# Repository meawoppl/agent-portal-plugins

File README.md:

# Agent Portal Plugins

This repository is a collection of test and reference plugins for
[Agent Portal](https://github.com/meawoppl/agent-portal). Each plugin lives in a
subdirectory and contains its own `agent-portal-plugin.toml` manifest.

## Interface Design

Agent Portal owns the session lifecycle, agent launch, authentication, work
queues, docked surfaces, and plugin discovery UI. This repository owns
domain-specific plugin packages: manifests, skills, prompts, command shims,
managed toolchains, and optional HTTP workbench surfaces.

The interface is intentionally manifest-first:

- `[[detect]]` patterns let Portal suggest plugins for a working directory before
  an agent is launched.
- `[[skills]]` and `[[prompts]]` describe context Portal can inject into agent
  sessions, with visible context-cost accounting in the Portal UI.
- `[[commands]]` define safe, named command surfaces that Portal and agents can
  call without learning each plugin's private shell layout.
- `[surface]` describes an optional local HTTP app that Portal can start and dock
  beside the conversation.
- `[install]` and `[[toolchains]]` keep plugin setup and health checks inside
  the plugin package instead of hard-coding domain tooling into Portal.

This split keeps Agent Portal generic while still making plugin capability
discoverable in the launch menu, session header, plugin dock, and collapsed
plugin-context notice.

Install any plugin from its subdirectory:

```console
agent-portal plugin install github:meawoppl/agent-portal-plugins//kicadmium
agent-portal plugin install github:meawoppl/agent-portal-plugins//visilog
agent-portal plugin install github:meawoppl/agent-portal-plugins//unlinked
agent-portal plugin install github:meawoppl/agent-portal-plugins//yapcad
agent-portal plugin install github:meawoppl/agent-portal-plugins//slowbooks
```

## Plugins

- [`slowbooks`](slowbooks/) - project-local SlowBooks Pro bookkeeping with the
  native browser UI, persistent company files, scoped API commands, and managed
  startup/restarts.

- [`visilog`](visilog/) - interactive design exploration with the native
  Visilog viewer: module hierarchy diagrams, live values, source inspection,
  stepping, breakpoints and JSON design graphs.
- [`unlinked`](unlinked/) - Simulink model review without MATLAB via
  [Unlinked](https://github.com/CosmicFrontierLabs/unlinked): SVG diagrams
  and subsystems, block inventories, the supported simulation subset with
  plotted traces, and MATLAB-to-Rust transpilation.
- [`yapcad`](yapcad/) - parametric [yapCAD](https://github.com/rdevaul/yapCAD)
  DSL workbench: retained builds with stats and previews, a live 3D/2D pane
  with sections, measurement and pinned annotations, STL/STEP/DXF/SVG
  exports, `.ycpkg` packages and assemblies.
- [`kicadmium`](kicadmium/) - all-Rust KiCad PCB/electronics workbench: one
  binary with a browser workbench, `kct` (a native port of kicad-tools) and
  `kct lint`. It replaces the former `kicad-pcb` plugin and lived in
  `meawoppl/kicadmium` (now archived) before moving here with its full history.

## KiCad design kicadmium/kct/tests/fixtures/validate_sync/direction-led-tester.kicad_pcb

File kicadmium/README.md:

# kicadmium

> The heavy metal your PCBs were missing.

Cadmium is a heavy metal; kicadmium is the one your boards needed. It reads
your whole board, tells you your vias are ugly, and it's right. kicadmium is a
single Rust binary that wraps a real KiCad install with a browser workbench
(schematic, PCB, Gerbers, 3D, BOM, libraries, checks), fabrication export,
layout-quality audits, and a pile of agent skills. It does not ship KiCad.
Bring your own and turn it up.

## Quick start

As an Agent Portal plugin:

```sh
agent-portal plugin install github:meawoppl/agent-portal-plugins//kicadmium
```

Install builds the binary with `scripts/setup.sh`. Cargo writes to
`target/install-build`; only after a successful build does Rust atomically
activate the complete executable at `bin/kicadmium`. Every portal command uses
that stable path, so the previous executable remains callable throughout a
rebuild. `doctor --json` reports `runtime.installation.rebuild_in_progress`.
Concurrent installs are refused via `.install-lock/pid`; after an interrupted
install, check that PID is no longer running before removing the lock.

The portal gives plugin
commands a private `HOME`, so the script points rustup, cargo, trunk and
sccache at the account's existing caches (otherwise every install downloads a
toolchain and the crate index afresh) and uses `sccache` as the rustc wrapper
when it is installed. A reinstall then recompiles only what changed: about a
minute when nothing did, two with a `kct` change, versus twenty cold.
`KICADMIUM_SETUP_PLAIN=1` disables all of that.

From a checkout of this directory:

```sh
rustup target add wasm32-unknown-unknown
cargo install trunk --locked

cargo run -p backend -- serve --port 48888 --cwd /path/to/hardware/repo
# -> http://127.0.0.1:48888/
```

## CLI

```sh
kicadmium doctor --json --cwd .          # what tools/projects he found
kicadmium drc --json --cwd . --project board-a
kicadmium erc --json --cwd .
kicadmium quality --json --cwd .         # kct rules + in-house audits vs qualityProfile
kicadmium lint --json --cwd .            # = kct lint run on the project board
kicadmium export gerbers --cwd . --out build/gerbers
kicadmium export jlcpcb  --cwd . --out build/jlcpcb
kicadmium setup                          # report the KiCad install he found
kicadmium kct --help                     # native Rust PCB automation
kicadmium kct  --cwd . -- readiness . --format json
kicadmium tool --cwd . -- kicad-cli version
# canonical board lint: adjacent policy, evidence-bound exceptions, CI bundle
kicadmium kct -- lint run board.kicad_pcb --fail-on error
kicadmium kct -- lint waive board.kicad_pcb FINDING_KEY --reason "intentional" --reviewer agent
kicadmium kct -- lint ci boards/*.kicad_pcb --out lint-results --fail-on error
```

Environment: `KICADMIUM_KICAD_CLI`/`KICAD_CLI` pick `kicad-cli`;
`KICADMIUM_LIBRARY_WORKERS` and `KICADMIUM_LIBRARY_CACHE_MB` tune library
renders. Native `kct` is part of the Kicadmium binary and needs no runtime
installation.

## JLCPCB placement corrections

When JLCPCB's part model does not match the KiCad footprint, record the
correction on the part with optional `JLCPCB Rotation Offset` and
`JLCPCB Position Offset` fields. Put them on the symbol (KiCad propagates them
to the footprint on *Update PCB from Schematic*) or directly on the footprint;
hide them on a Fab layer so silkscreen stays clean.

| Field | Value | Meaning |
|-------|-------|---------|
| `JLCPCB Rotation Offset` | degrees, e.g. `-90` | added to KiCad's rotation; `-90` is a quarter turn clockwise |
| `JLCPCB Position Offset` | `x,y` in mm, e.g. `0,-2.75` | footprint-local offset, KiCad +Y down, before rotation/flip |

Corrections stay attached to the footprint as the part moves, rotates, or
flips. `export jlcpcb` logs every corrected reference and writes
`<board>-placement-corrections.json` beside the CPL; the Libraries tab shows a
`JLC corr.` badge for corrected parts. The old `manufacturer.placementOffsets`
or `docs/jlcpcb-placement-offsets.json` table is still read as a deprecated
fallback for parts without fields, and part fields win over table entries.

## Layout

See [AGENTS.md](AGENTS.md). Rust workspace: `backend/` (Axum + CLI),
`frontend/` (Yew and embedded viewers), `shared/` (typed protocols), and
`kct/` (the native kicad-tools port, including the `kct lint` engine with 101
read-only, evidence-aware review rules). The linter is a
heuristic reviewer, not native ERC/DRC and not permission to edit your board.
Its canonical lifecycle is `kicadmium kct -- lint`; see
[docs/lint.md](docs/lint.md) for board-local exceptions, routing gates, and CI
artifacts.

The design rules we stole on purpose—and the places where we refuse to fake
certainty—are in [docs/design-principles.md](docs/design-principles.md).

## Inspirations

Ported out of the Agent Portal `kicad-pcb` plugin and built in the pattern of
[single-binary-rust-website](https://github.com/meawoppl/single-binary-rust-website).
It steals ideas shamelessly from:

- [Copperhead](https://github.com/copperheadhq/copperhead), for treating electronics design as an agent-native engineering workspace.
- [i2cjak/Backplane](https://github.com/i2cjak/Backplane), for truthful multi-view hardware inspection, revision-aware UI state, and its broader agent-driven electronics conventions.
- [i2cjak/Backplane_KiCad](https://github.com/i2cjak/Backplane_KiCad), Backplane's focused KiCad IPC fork.
- [rjwalters/kicad-tools](https://github.com/rjwalters/kicad-tools), for machine-readable inspection, validation, manufacturing, and mutation contracts.
- Thea Flowers' [KiCanvas](https://github.com/theacodes/kicanvas) and [Gingerbread](https://github.com/wntrblm/Gingerbread), for making KiCad designs genuinely useful in the browser and treating PCB output as a creative, inspectable medium.
- [American-Embedded/kistack](https://github.com/American-Embedded/kistack), for the practical KiCad agent workflows vendored here.
- [pastebom.com](https://github.com/meawoppl/pastebom.com), for reusable Rust PCB extraction and Gerber-viewing machinery, the `eda-view` crate's scene model (`vector`), its Yew canvas/schematic components (`components`), and the filesystem-free schematic renderer (`schematic`, `kicad`, `strokes`). See [docs/third-party.md](docs/third-party.md).
- [punkfab/circuit-skills](https://github.com/punkfab/circuit-skills), for its simulate-then-lay-out workflow and its record of verification gates that gave false passes. Ideas only: the repository has no licence, so none of its code or text is used.
- [parisxmas/fastroute](https://github.com/parisxmas/fastroute), a Rust port of Freerouting, for its unrouted-connection diagnosis, best-so-far checkpoints and benchmark boards. It is GPL-3.0-or-later, so if kicadmium uses it, it runs as a separate, discovered program; none of its code is linked or vendored.

### Fast regional feedback

`kicadmium drc --project ID --region X0 Y0 X1 Y1 --margin 2` runs native local copper/zone-clearance and courtyard checks. `kicadmium kct -- lint run BOARD --region X0 Y0 X1 Y1 --margin 2` runs a declared set of local trace/via/pad rules. Both print structured results with `engine: native-local`, explicit coverage, and `requires_full_verification: true`.

The regional snapshot retains intersecting objects and a guard margin, including crossing segments and neighboring pads. Content-addressed caches in `.kct-region-cache` include scoped geometry, bounds, margin, rule configuration, adjacent project/custom rules, policy bytes and engine version. Edits wholly outside the snapshot reuse local results; the reported board hash still reflects the current full board. Source boards are never written.

Regional checks are a partial fast-feedback path, not full KiCad DRC, schematic parity, global connectivity, or complete lint. Conditional custom DRC rules fail explicitly in native regional DRC. Always run full `verify` before commit; omitting `--region` preserves the existing full-check behavior.
### Regional before/after rendering

`kicadmium render --project ID --region 170 20 15 12 --layers F.Cu,F.SilkS,Edge.Cuts --zones net=VIN_5V --baseline HEAD -o region.png` produces a labeled comparison directly from board geometry. The region is x/y/width/height in millimetres; omit `--baseline` for the working board alone. A baseline can also be a board file. `--zones none|filled|net=NAME` controls existing fill polygons, `--highlight-nets GND,VIN_5V` highlights copper, and `--annotation` outlines the region. SVG and PNG have an opaque Tokyo-Night background. Baselines are read with Git, never checked out; rendering does not refill or save a board. Unfilled zones have no fill polygons to show. Publish the result with `agent-portal show region.png`.
### Supervised workbench (Linux user systemd)

Run the installed `bin/kicadmium surface ensure --cwd /path/to/project --port 8765` to start or reuse a workbench outside the Portal session's cgroup. It prints the local URL after the listener starts. Forward that port with `agent-portal forward 8765` for remote access. Processes restart automatically on failure and survive Portal service restarts; the Portal forwarding URL itself is session-owned and may need to be reopened by Portal.

Successful plugin activation restarts registered workbench units against the newly activated stable executable. Unit names are deterministic for each project directory and port, so repeated `ensure` calls reuse the same process. Inspect logs with `journalctl --user -u 'kicadmium-surface-*'`. This requires a running Linux user systemd manager; transient services last for that manager's lifetime, not across machine reboots. `serve` remains available for other platforms and Portal-managed hosting.

The Portal manifest runs `serve` in the foreground so Portal's managed-service launcher owns its lifetime, injects the port, and restores it after session or launcher restarts. Use an updated Portal launcher with managed-forward support for that recovery behavior. The standalone `surface ensure` command remains available outside managed hosting; on macOS it bootstraps a service into the current GUI user's launchd domain with `KeepAlive`. Neither standalone platform requires a root/system service. Readiness requires a successful kicadmium `/healthz` response, and a port occupied outside the selected unit is rejected.
PCB region annotations queue the note, image, region and view revision without waiting for analysis. Optional context is fetched in the background while composing: intersecting footprints, copper nets by layer, a SHA-256 board revision and quality findings already cached for those inputs. Ready context is attached only for the same project, revision and region, capped below 40 lines with an explicit omitted count. Pending or failed context never blocks sending. This path does not run lint, start quality builds, or modify an already queued annotation. Changing the project, view or revision clears the old selection so its screenshot is not attached to a different board revision. Schematic annotations also carry the open sheet path as `context.sheet` (and a "Schematic sheet:" line in the note), since every sheet shares one paper coordinate frame.
### One-shot verification

`kicadmium verify --project ID --baseline HEAD --json` runs full DRC (including schematic parity), ERC, lint, lint-exception stale checks, quality, and declared derived-document checks. Both working inputs and Git baselines are checked in disposable snapshots; a baseline board file can also be supplied with current project context. No board swapping or source saves occur.

Output uses `kicadmium.verify/v1`, with per-stage before/after counts, added/removed findings, and groups by rule and nets. Omit `--json` for a concise summary (seven lines when unchanged). `--gate error|warning|never` controls newly introduced finding failures; an incomplete stage always fails. Without a baseline, all current findings are considered new. Ignored lint findings do not fail the gate.

Caches include the complete selected source snapshot, executable hash, KiCad version and project identity. Git baselines cache by immutable commit; expiring lint decisions invalidate their cached report at expiry. Failed/incomplete stages are not cached. Full verification is the pre-commit gate; regional checks remain partial feedback.

### Find components and nets in the viewers

Use the small top-left search in Schematic, PCB, and 3D. It matches component
references, component values, and net names case-insensitively. An exact name
wins over partial matches (so `U1` does not also select `U10`); otherwise the
query is a literal substring. Clear or press Escape to remove the highlight.
On narrow screens the input is collapsed behind **Search**.

Schematic search highlights matching symbols and net geometry and opens a
matching sheet when the current sheet has no match. PCB search highlights
matching footprints or net geometry while respecting the visible layers.
The 3D viewer outlines matching component models in orange; a net search
outlines the components connected to it. KiCad's exported GLB does not retain
per-net copper identities, so 3D search does not claim to highlight individual
tracks. The 3D count reports models actually outlined, including zero when a
matching component has no model. Searching never rebuilds the board or runs
checks, and clearing it restores the normal view without moving the camera.

Parts lookup falls back to the EasyEDA product API when JLCPCB's catalog endpoint
is unavailable. JSON records include `source` and `stock_source`; EasyEDA's LCSC
stock is distributor inventory, not JLCPCB assembly inventory. Unknown stock is
reported as unknown by `parts availability`. Exact LCSC-number searches support
this fallback too. Keyword search still requires the JLCPCB search service and
reports a capability error with its endpoint/status if unavailable.

`kct detect-mistakes` treats USB speed as unknown unless a skew budget is
explicitly supplied. Use repeatable `--pair-skew 'USB_D+,USB_D-,2'` for a
reviewed 2 mm budget, or supply the budget required by the actual interface and
device. An undeclared USB pair produces an informational finding; it never
inherits a High-Speed error threshold merely from its net names.

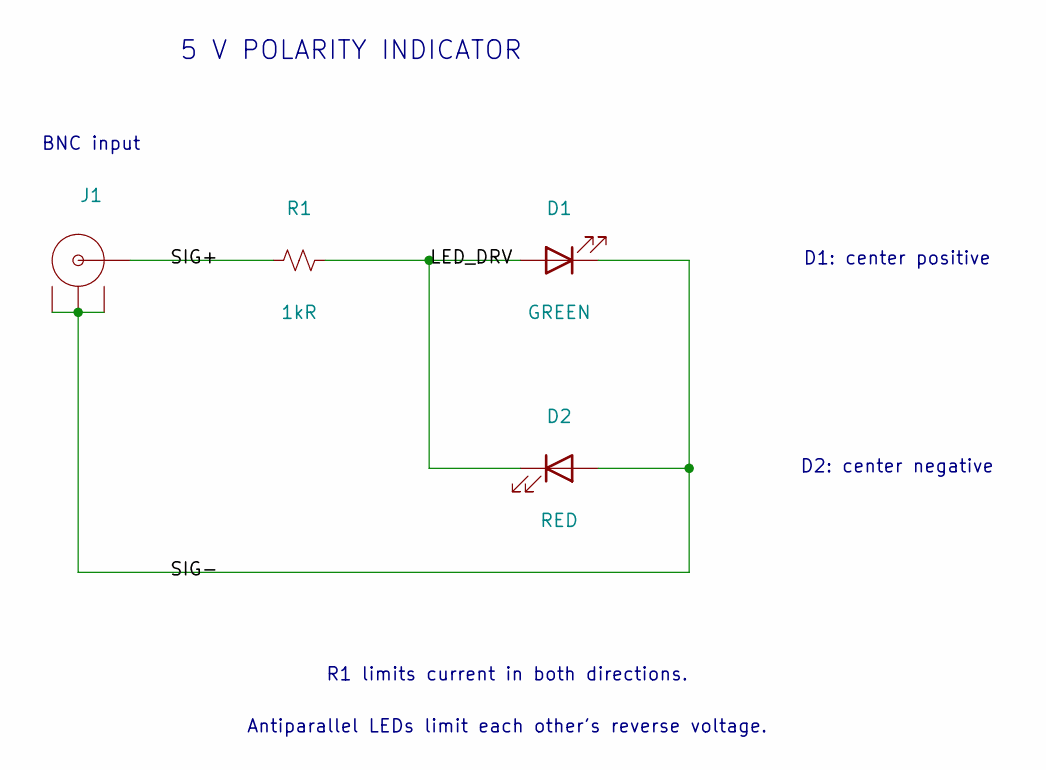
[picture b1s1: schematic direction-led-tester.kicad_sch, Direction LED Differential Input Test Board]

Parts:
D1: GREEN; LED_1206_3216Metric; MPN LTST-C150GKT; LCSC Part C125084
D2: RED; LED_1206_3216Metric; MPN LTST-C150KRKT; LCSC Part C125086
J1: KH-BNC50-3511; ANT-TH_KH-BNC50-3511; LCSC Part C2837587
R1: 1kR; R_0805_2012Metric; MPN 0805W8F1001T5E; LCSC Part C17513

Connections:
/LED_DRV: D1.2 (A), D2.1 (K), R1.2
/SIG+: J1.1 (OUT), R1.1
/SIG-: D1.1 (K), D2.2 (A), J1.2, J1.3, J1.4

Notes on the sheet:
5 V POLARITY INDICATOR
BNC input
D1: center positive
D2: center negative
R1 limits current in both directions.
Antiparallel LEDs limit each other's reverse voltage.

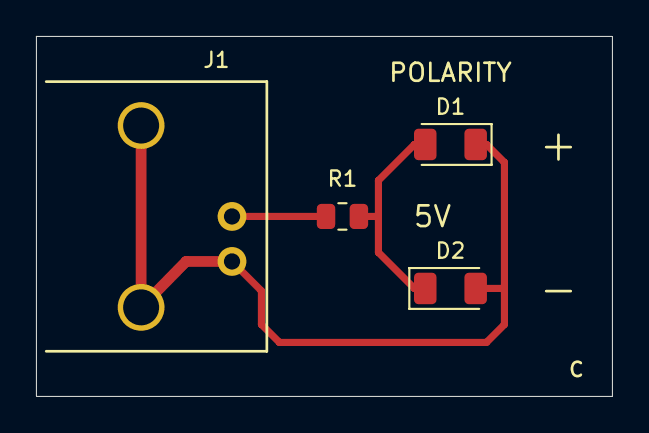
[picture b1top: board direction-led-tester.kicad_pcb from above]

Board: 2 copper layers, 32.0 x 20.0 mm, 4 parts (0 on the bottom side), 3 nets.

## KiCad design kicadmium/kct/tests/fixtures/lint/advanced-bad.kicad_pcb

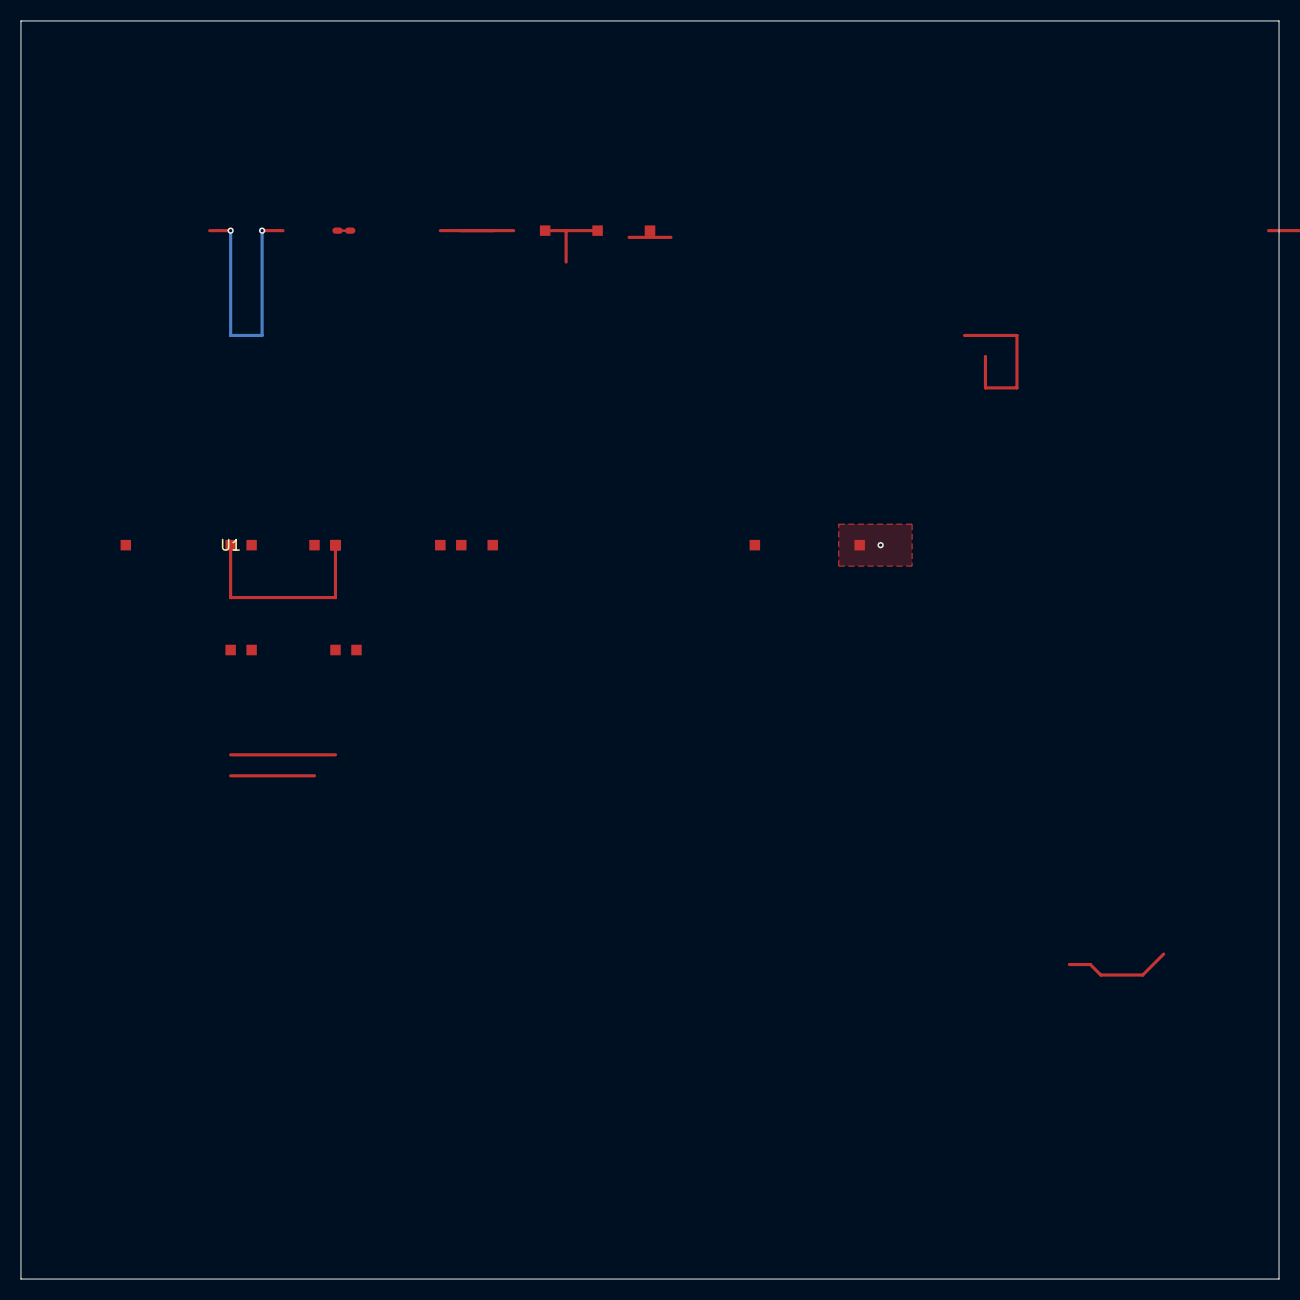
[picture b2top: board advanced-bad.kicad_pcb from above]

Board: 2 copper layers, 120.0 x 120.0 mm, 13 parts (0 on the bottom side), 4 nets.

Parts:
C1: 100n; Device
EXTA: 10k; Device
EXTB: 10k; Device
GRAZE: 10k; Device
J1: 10k; Device
P1, P2: 10k; Device
R1: 10k; Device
THERM: 10k; Device
TP1: 10k; Device
TPG: 10k; Device
U1, U2: 10k; Device

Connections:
A: C1.1, EXTA.1, R1.1, TP1.1, U1.1, U2.2
B: EXTB.1, U1.2, U2.1
GND: C1.2, J1.2, R1.2, THERM.1, TPG.1
P: P1.1, P2.1

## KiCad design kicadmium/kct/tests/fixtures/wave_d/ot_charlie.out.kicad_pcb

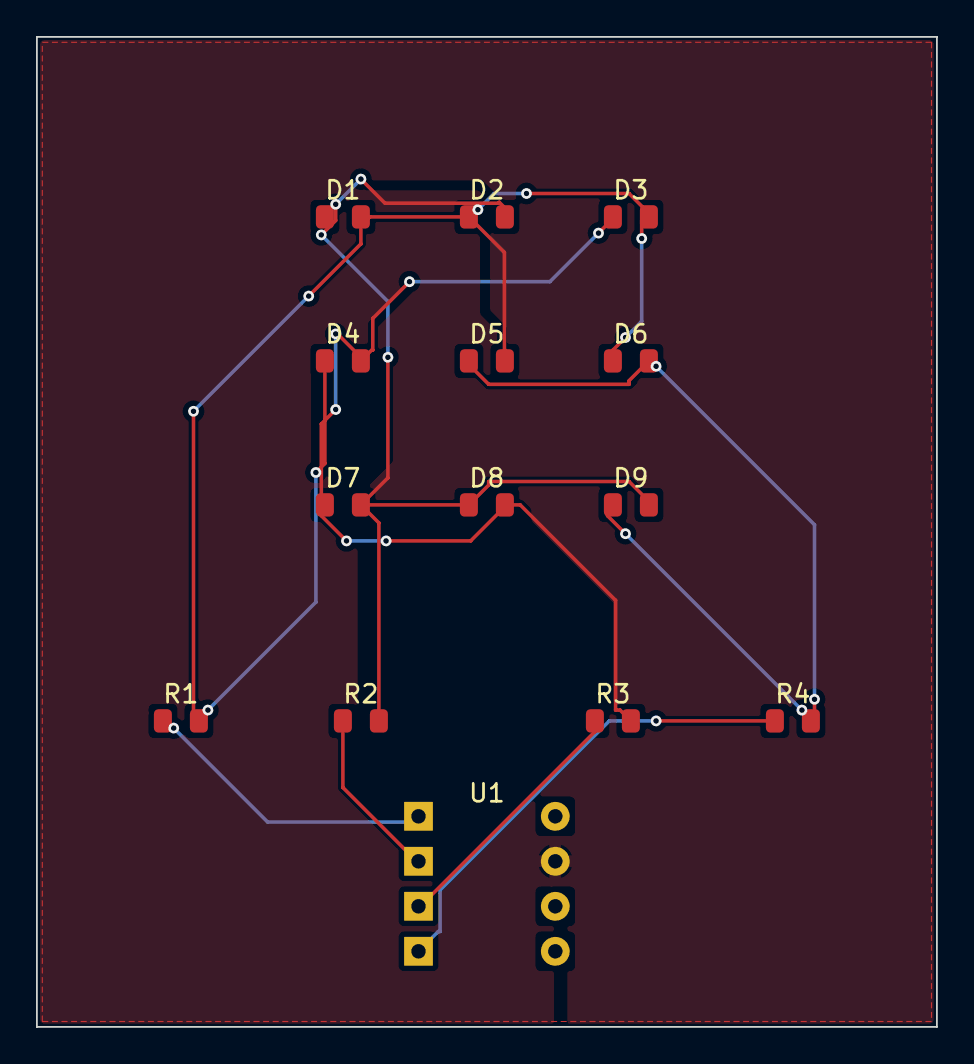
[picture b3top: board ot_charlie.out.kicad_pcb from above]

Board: 2 copper layers, 50.0 x 55.0 mm, 14 parts (0 on the bottom side), 9 nets.

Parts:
D1, D2, D3, D4, D5, D6, D7, D8, D9: LED; LED_0805_2012Metric
R1, R2, R3, R4: 330R; R_0805_2012Metric
U1: MCU; DIP-8_W7.62mm

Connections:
GND: U1.5, U1.6, U1.8
LINE_A: R1.1, U1.1
LINE_B: R2.1, U1.2
LINE_C: R3.1, U1.3
LINE_D: R4.1, U1.4
NODE_A: D1.2, D2.1, D3.2, D4.1, D5.2, D6.1, R1.2
NODE_B: D1.1, D2.2, D7.2, D8.1, D9.2, R2.2
NODE_C: D3.1, D4.2, D7.1, D8.2, R3.2
NODE_D: D5.1, D6.2, D9.1, R4.2

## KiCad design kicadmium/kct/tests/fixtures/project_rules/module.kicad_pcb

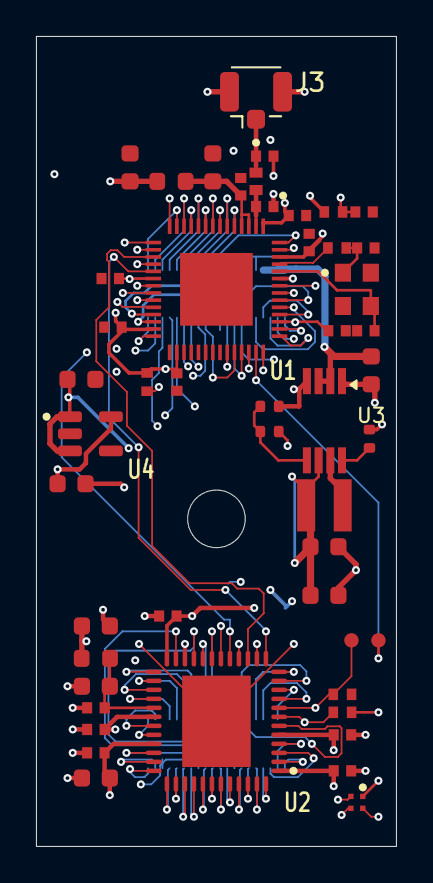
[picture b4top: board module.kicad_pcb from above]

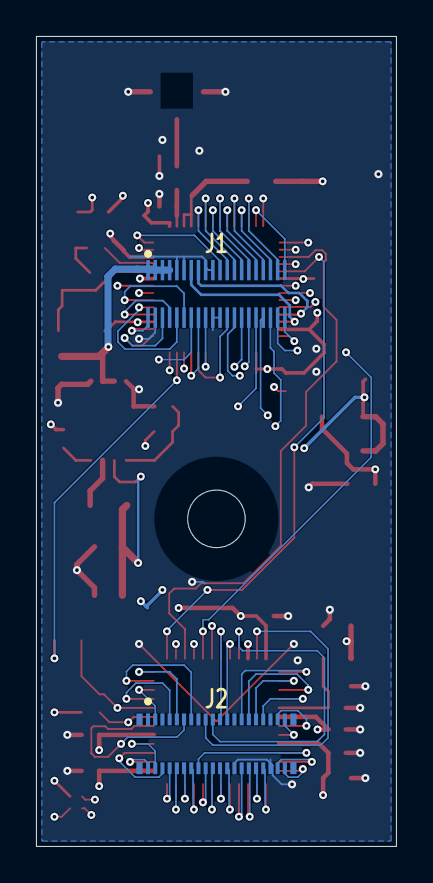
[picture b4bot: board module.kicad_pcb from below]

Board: 4 copper layers, 20.0 x 45.0 mm, 52 parts (2 on the bottom side), 84 nets.

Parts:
C1: 3.3pF; C1_CAPC1005X60
C2: 3.3pF; C2_CAPC1005X60
C6: 12pF; C6_CAPC1005X60
C7: 12pF; C7_CAPC1005X60
C32: 1uF; C32_CAPC1005X60
C33: 10uF; C33_C_0603_1608Metric
C34: 10uF; C34_C_0603_1608Metric
C35: 0.1uF; C35_CAPC1005X60
C37: 0.1uF; C37_CAPC1005X60
C38: 0.1uF; C38_CAPC1005X60
C39: 0.1uF; C39_CAPC1005X60
C40: 0.1uF; C40_CAPC1005X60
C41: 0.1uF; C41_CAPC1005X60
C42: 0.1uF; C42_CAPC1005X60
C43: 10uF; C43_C_0603_1608Metric
C44: 0.1uF; C44_CAPC1005X60
C45: 10uF; C45_C_0603_1608Metric
C46: 0.1uF; C46_CAPC1005X60
C48: 0.1uF; C48_CAPC1005X60
C49: 0.1uF; C49_CAPC1005X60
C50: 0.1uF; C50_CAPC1005X60
C52: 0.1uF; C52_CAPC1005X60
C60: 10uF / 10V; C60_C_0603_1608Metric
C61: 22uF / 10V; C61_C_0603_1608Metric
C62: 1uF / 6.3V; C62_C_0603_1608Metric
C63: 1uF / 6.3V; C63_C_0603_1608Metric
C66: 1uF / 6.3V; C66_C_0603_1608Metric
C67: 22uF / 10V; C67_C_0603_1608Metric
D1: FC-B1010RGBT-HG; D1_RGBLED
H1: MountingHole_3.2mm_M3
J1: DF40C(2.0)-40DS-0.4V(51); J1_DF40C_40DS_2mm
J2: DF40C-40DP-0.4V(51); J2_DF40C_40DP
J3: U.FL-R-SMT-1(01); J3_U.FL_Hirose_U.FL-R-SMT-1_Vertical
L1: 100ohm @100MHz; L1_L_0603_1608Metric
L2: 100ohm @100MHz; L2_L_0603_1608Metric
L3: 2.2nH; L3_INDC1006X60N
L4: 2.2uH; L4_L_XFL3012_222MEC
R3: 0R; R3_RESC1005X40
R20: 10kR; R20_RESC1005X40
R22: 10kR; R22_RESC1005X40
R28: 10kR; R28_RESC1005X40
R29: 10kR; R29_RESC1005X40
R62: 100kR; R62_R_0402_1005Metric
R64: 75kR; R64_R_0402_1005Metric
R65: 24kR; R65_R_0402_1005Metric
TP1: FPGA_CRESET_N; TestPoint_0p8
TP2: FPGA_CDONE; TestPoint_0p8
U1: ESP32-S2FH4; U1_QFN56_ESP32-S2FH4_EXP-M
U2: iCE40UP5K-SG48; U2_ICE40-QFN
U3: TPS62160DGKR; U3_VSSOP-8_3x3mm_P0.65mm
U4: TLV75512PDBVR; U4_SOT-23-5
Y1: 40MHz / CL10pF; Y1_JGHC_S2240000101050

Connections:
+1.2V: C45.1, C49.1, C50.1, C63.1, L2.1, U2.5, U2.30, U4.5
+1.2V_PLL: C43.1, C44.1, L2.2, U2.29
+3.3V: C33.1, C37.1, C38.1, C39.1, C40.1, C41.1, C42.1, C46.1, C48.1, C52.1, C61.1, C62.1, C66.1, C67.1, D1.P$1, L1.1, L4.2, R20.2, R22.2, R29.2, R62.2, R64.1, U1.1, U1.20, U1.27, U1.30, U1.45, U1.51, U1.54, U2.1, U2.22, U2.24, U2.33, U3.6, U4.1, U4.3
/BUCK_FB: R64.2, R65.1, U3.5
/BUCK_SW: L4.1, U3.7
/ESP_EN: C32.1, J1.11, R22.1, U1.56
/ESP_GPIO0_BOOT: J1.12, R20.1, U1.5
/ESP_GPIO1: J1.13, U1.6
/ESP_GPIO2: J1.14, U1.7
/ESP_GPIO3: J1.15, U1.8
/ESP_GPIO4: J1.16, U1.9
/ESP_GPIO5: J1.17, U1.10
/ESP_GPIO6: J1.18, U1.11
/ESP_GPIO7: J1.19, U1.12
/ESP_GPIO8: J1.20, U1.13
/ESP_GPIO15: J1.35, U1.21
/ESP_GPIO16: J1.37, U1.22
/ESP_GPIO17: J1.36, U1.23
/ESP_GPIO18: J1.38, U1.24
/ESP_GPIO21: J1.40, U1.28
/ESP_GPIO33: J1.29, U1.37
/ESP_GPIO34: J1.32, U1.38
/ESP_GPIO35: J1.28, U1.39
/ESP_GPIO38: J1.39, U1.42
/ESP_GPIO39: J1.23, U1.43
/ESP_GPIO40: J1.21, U1.44
/ESP_GPIO41: J1.24, U1.46
/ESP_GPIO42: J1.25, U1.47
/ESP_GPIO43_TXD: J1.26, U1.48
/ESP_GPIO44_RXD: J1.27, U1.49
/ESP_GPIO45: J1.34, U1.50
/ESP_GPIO46: J1.33, U1.55
/FPGA_CDONE: R29.1, TP2.1, U1.41, U2.7
/FPGA_CRESET_N: R28.2, TP1.1, U1.40, U2.8
/FPGA_IOB_0A: J2.35, U2.46
/FPGA_IOB_2A: J2.36, U2.47
/FPGA_IOB_3B_G6: J2.32, U2.44
/FPGA_IOB_4A: J2.37, U2.48
/FPGA_IOB_5B: J2.34, U2.45
/FPGA_IOB_6A: J2.40, U2.2
/FPGA_IOB_8A: J2.39, U2.4
/FPGA_IOB_9B: J2.38, U2.3
/FPGA_IOB_13B: J2.6, U2.6
/FPGA_IOB_16A: J2.4, U2.9
/FPGA_IOB_18A: J2.2, U2.10
/FPGA_IOB_20A: J2.7, U2.11
/FPGA_IOB_22A: J2.5, U2.12
/FPGA_IOB_23B: J2.10, U2.21
/FPGA_IOB_25B_G3: J2.12, U2.20
/FPGA_IOB_29B: J2.11, U2.19
/FPGA_IOT_36B: J2.14, U2.25
/FPGA_IOT_37A: J2.9, U2.23
/FPGA_IOT_38B: J2.15, U2.27
/FPGA_IOT_39A: J2.16, U2.26
/FPGA_IOT_41A: J2.17, U2.28
/FPGA_IOT_42B: J2.19, U2.31
/FPGA_IOT_43A: J2.20, U2.32
/FPGA_IOT_44B: J2.33, U2.34
/FPGA_IOT_45A_G1: J2.24, U2.37
/FPGA_IOT_46B_G0: J2.22, U2.35
/FPGA_IOT_48B: J2.21, U2.36
/FPGA_IOT_49A: J2.31, U2.43
/FPGA_IOT_50B: J2.25, U2.38
/FPGA_IOT_51A: J2.30, U2.42
/FPGA_RGB0: D1.P$2, J2.26, U2.39
/FPGA_RGB1: D1.P$3, J2.27, U2.40
/FPGA_RGB2: D1.P$4, J2.29, U2.41
/LINK_CS_N: U1.15, U2.16
/LINK_IO2: U1.19, U2.13
/LINK_IO3: U1.14, U2.18
/LINK_MISO: U1.18, U2.14
/LINK_MOSI: U1.16, U2.17
/LINK_SCK: U1.17, U2.15
/PG_3V3: R62.1, U3.8
/RF_ANT: C2.1, J3.1, L3.2
/RF_IN: C1.1, L3.1, U1.2
/USB_D+: J1.7, U1.26
/USB_D-: J1.8, U1.25
/XTAL_N: C7.1, U1.52, Y1.OUT/IN
/XTAL_P: R3.1, U1.53
/XTAL_P_CRYSTAL: C6.1, R3.2, Y1.IN/OUT
ESP_VDD3P3: C34.1, C35.1, L1.2, U1.3, U1.4
GND: C1.2, C2.2, C6.2, C7.2, C32.2, C33.2, C34.2, C35.2, C37.2, C38.2, C39.2, C40.2, C41.2, C42.2, C43.2, C44.2, C45.2, C46.2, C48.2, C49.2, C50.2, C52.2, C60.2, C61.2, C62.2, C63.2, C66.2, C67.2, J1.5, J1.6, J1.9, J1.10, J1.22, J1.30, J1.31, J2.1, J2.3, J2.8, J2.13, J2.18, J2.23, J2.28, J3.2, R28.1, R65.2, U1.57, U2.PAD, U3.1, U3.4, U4.2, Y1.GND-A, Y1.GND-B
VIN_5V: C60.1, J1.1, J1.2, J1.3, J1.4, U3.2, U3.3
